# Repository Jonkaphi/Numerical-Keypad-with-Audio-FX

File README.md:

# Mechanical Numerical Keypad with local Audio FX
The desire to make this little keypad came from idea to reuse a some of the parts from a broken keyboard someone gave me.

The extra little feature of having audio fx being played locally on the keyboard with each button press, was from one of the commenters on reddit related to a post. The sound files will be read from the placed SD card. Currently the audio that can be played is from 8 to 16 kHz kHz sample rate with 16 bit signed PCM.

The lower level sd card interface for the file system used in the project was made by Khaled Magdy in their post on 

### Top View

### Bottom View

## Issues as of 08/2025
* Current USB port part is not vertically offset, which collides with the PCB, read "Connectors" page in the schematic.
* Encoder for PC system audio still glitches at times, but its significantly better compared to previous build versions
* Audio streaming and polling of the key inputs is done on a single thread, resulting in less than satisfactory responsiveness

## Future work
* Move to a MCU series that include SDIO for the SD card, has more flash to as to implement some sort of RTOS, and or has a second core to handle the audio streaming.
* General rework of the PCB, redesign of the audio front-end to have better amplification of the DAC data stream.

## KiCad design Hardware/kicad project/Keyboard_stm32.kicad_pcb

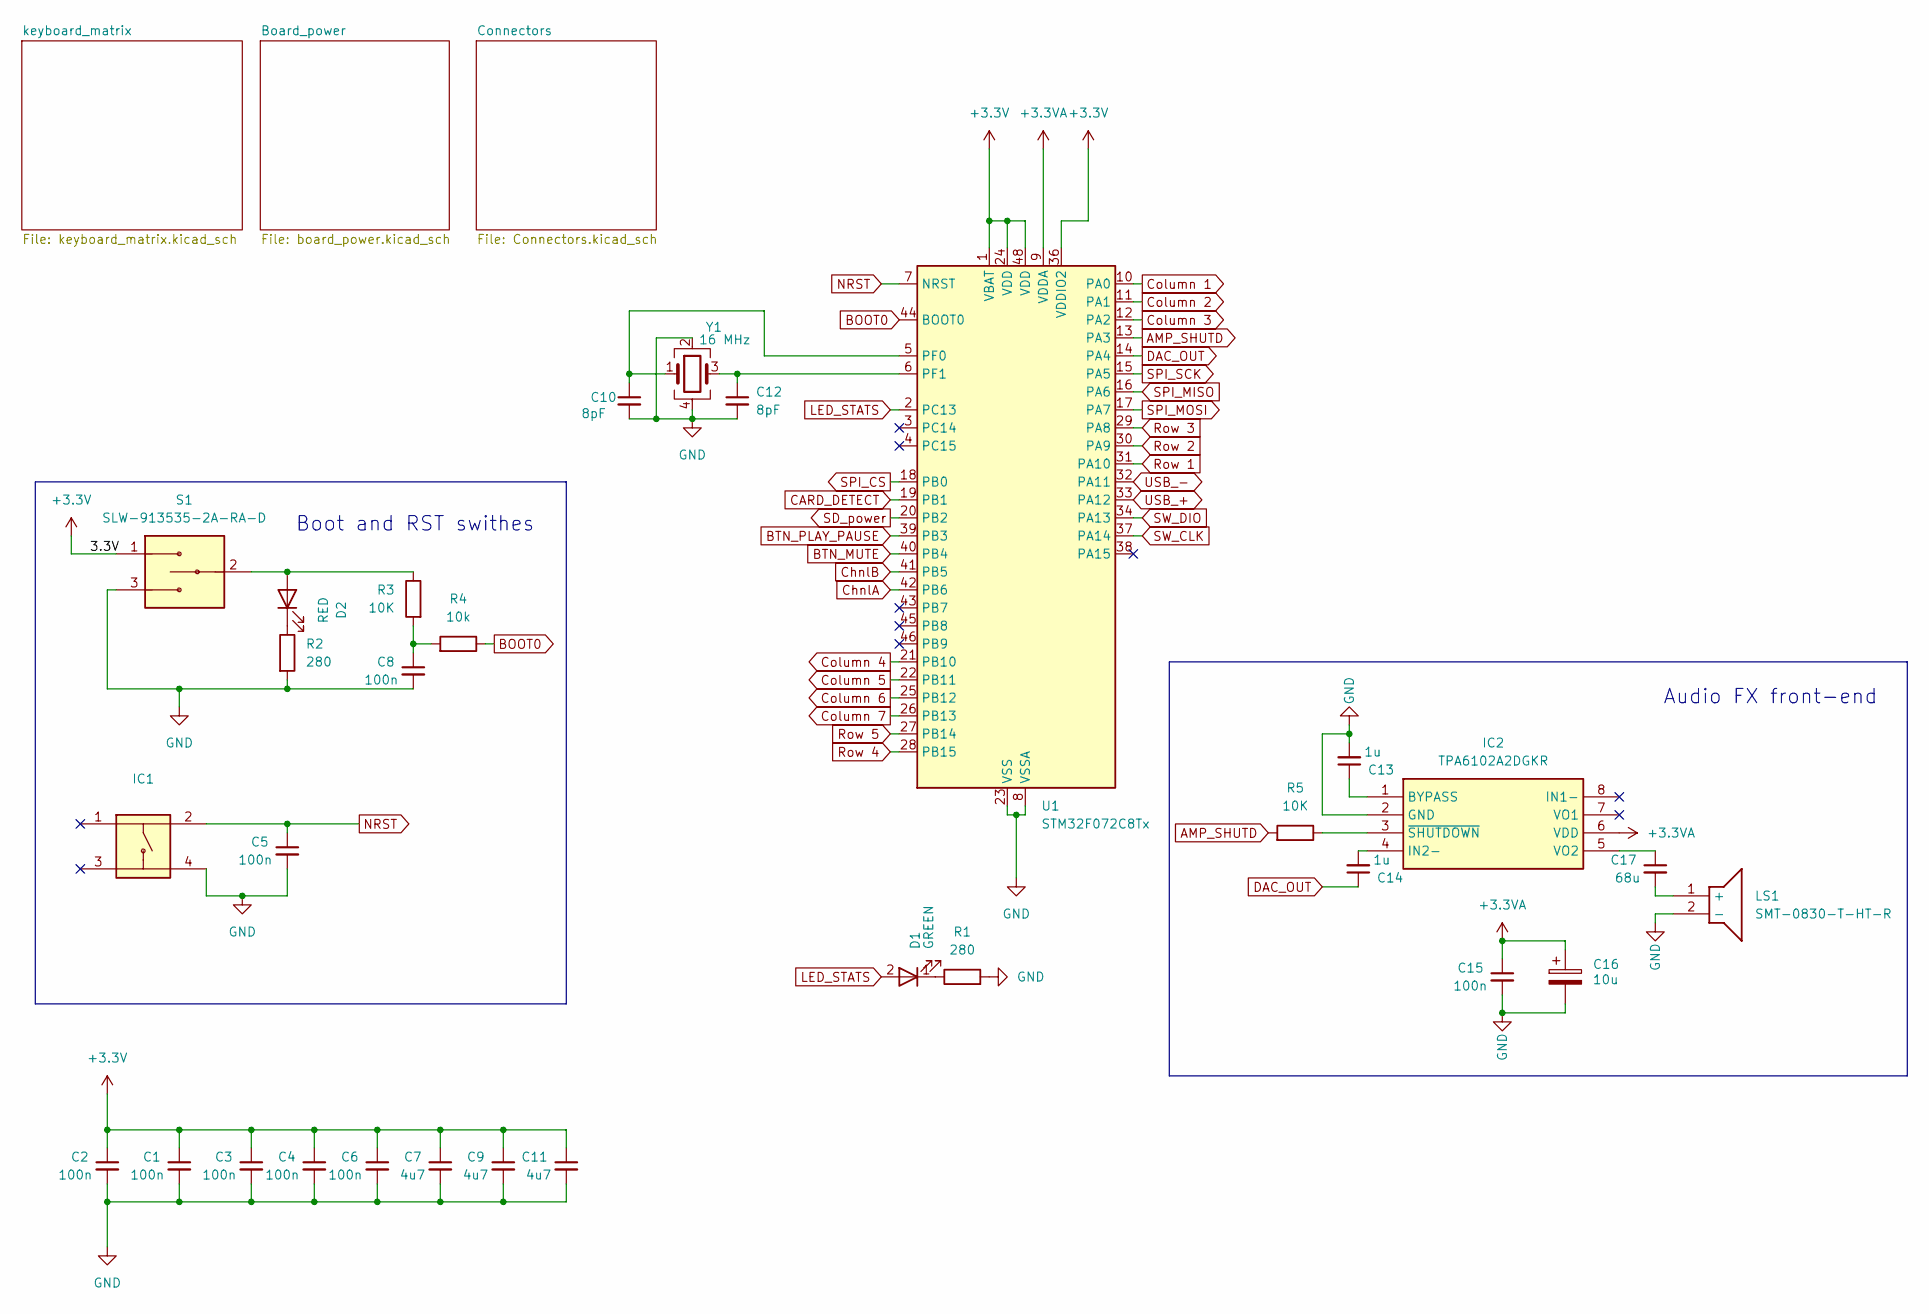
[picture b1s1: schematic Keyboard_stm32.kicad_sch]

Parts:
C1, C2, C3, C4, C5, C6, C8, C15: 100n; C_0805_2012Metric_Pad1.18x1.45mm_HandSolder
C7, C9, C11: 4u7; C_0805_2012Metric_Pad1.18x1.45mm_HandSolder
C10, C12: 8pF; C_0603_1608Metric_Pad1.08x0.95mm_HandSolder
C13, C14: 1u; C_0805_2012Metric_Pad1.18x1.45mm_HandSolder
C16: 10u; CAPPRD200W52D500H1250
C17: 68u; C_1206_3216Metric_Pad1.33x1.80mm_HandSolder
D1: GREEN; 150080VS75000
D2: RED; 150080VS75000
IC1: TS02-66-80-BK-160-LCR-D; TS026680BK160LCRD; Manufacturer_Part_Number TS02-66-80-BK-160-LCR-D; Mouser Part Number 179-TS026680BK160LCR
IC2: TPA6102A2DGKR; SOP65P490X110-8N; Manufacturer_Part_Number TPA6102A2DGKR; Mouser Part Number 595-TPA6102A2DGKR
LS1: SMT-0830-T-HT-R; Manufacturer_Part_Number TE122001-6; Mouser Part Number 497-TE122001-6
R1, R2: 280; R_0603_1608Metric_Pad0.98x0.95mm_HandSolder
R3, R5: 10K; R_0603_1608Metric_Pad0.98x0.95mm_HandSolder
R4: 10k; R_0603_1608Metric_Pad0.98x0.95mm_HandSolder
S1: SLW-913535-2A-RA-D; Manufacturer_Part_Number EG1218; Mouser Part Number 612-EG1218
U1: STM32F072C8Tx; LQFP-48_7x7mm_P0.5mm
Y1: 16 MHz; TSX-3225_16.0000MF09Z-AC3

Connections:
AMP_SHUTD: R5.2, U1.13 (PA3)
BOOT0: R4.1, U1.44 (BOOT0)
BTN_MUTE: U1.40 (PB4); also elsewhere on the board
BTN_PLAY_PAUSE: U1.39 (PB3); also elsewhere on the board
CARD_DETECT: U1.19 (PB1); also elsewhere on the board
ChnlA: U1.42 (PB6); also elsewhere on the board
ChnlB: U1.41 (PB5); also elsewhere on the board
Column 1: U1.10 (PA0); also elsewhere on the board
Column 2: U1.11 (PA1); also elsewhere on the board
Column 3: U1.12 (PA2); also elsewhere on the board
Column 4: U1.21 (PB10); also elsewhere on the board
Column 5: U1.22 (PB11); also elsewhere on the board
Column 6: U1.25 (PB12); also elsewhere on the board
Column 7: U1.26 (PB13); also elsewhere on the board
DAC_OUT: C14.1, U1.14 (PA4)
LED_STATS: D1.2, U1.2 (PC13)
NRST: C5.1, IC1.2, U1.7 (NRST); also elsewhere on the board
unnamed: C8.1, R3.2, R4.2
unnamed: D1.1, R1.1
unnamed: D2.2 (A), R3.1, S1.2
unnamed: D2.1 (K), R2.1
unnamed: C13.1, IC2.1 (BYPASS)
unnamed: C14.2, IC2.4 (IN2-)
unnamed: C17.1, IC2.5 (VO2)
unnamed: IC2.3 (~SHUTDOWN), R5.1
unnamed: C17.2, LS1.1 (+)
unnamed: C10.1, U1.5 (PF0), Y1.1
unnamed: C12.1, U1.6 (PF1), Y1.3
Row 1: U1.31 (PA10); also elsewhere on the board
Row 2: U1.30 (PA9); also elsewhere on the board
Row 3: U1.29 (PA8); also elsewhere on the board
Row 4: U1.28 (PB15); also elsewhere on the board
Row 5: U1.27 (PB14); also elsewhere on the board
SD_power: U1.20 (PB2); also elsewhere on the board
SPI_CS: U1.18 (PB0); also elsewhere on the board
SPI_MISO: U1.16 (PA6); also elsewhere on the board
SPI_MOSI: U1.17 (PA7); also elsewhere on the board
SPI_SCK: U1.15 (PA5); also elsewhere on the board
SW_CLK: U1.37 (PA14); also elsewhere on the board
SW_DIO: U1.34 (PA13); also elsewhere on the board
USB_+: U1.33 (PA12); also elsewhere on the board
USB_-: U1.32 (PA11); also elsewhere on the board

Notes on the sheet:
Boot and RST swithes
Audio FX front-end

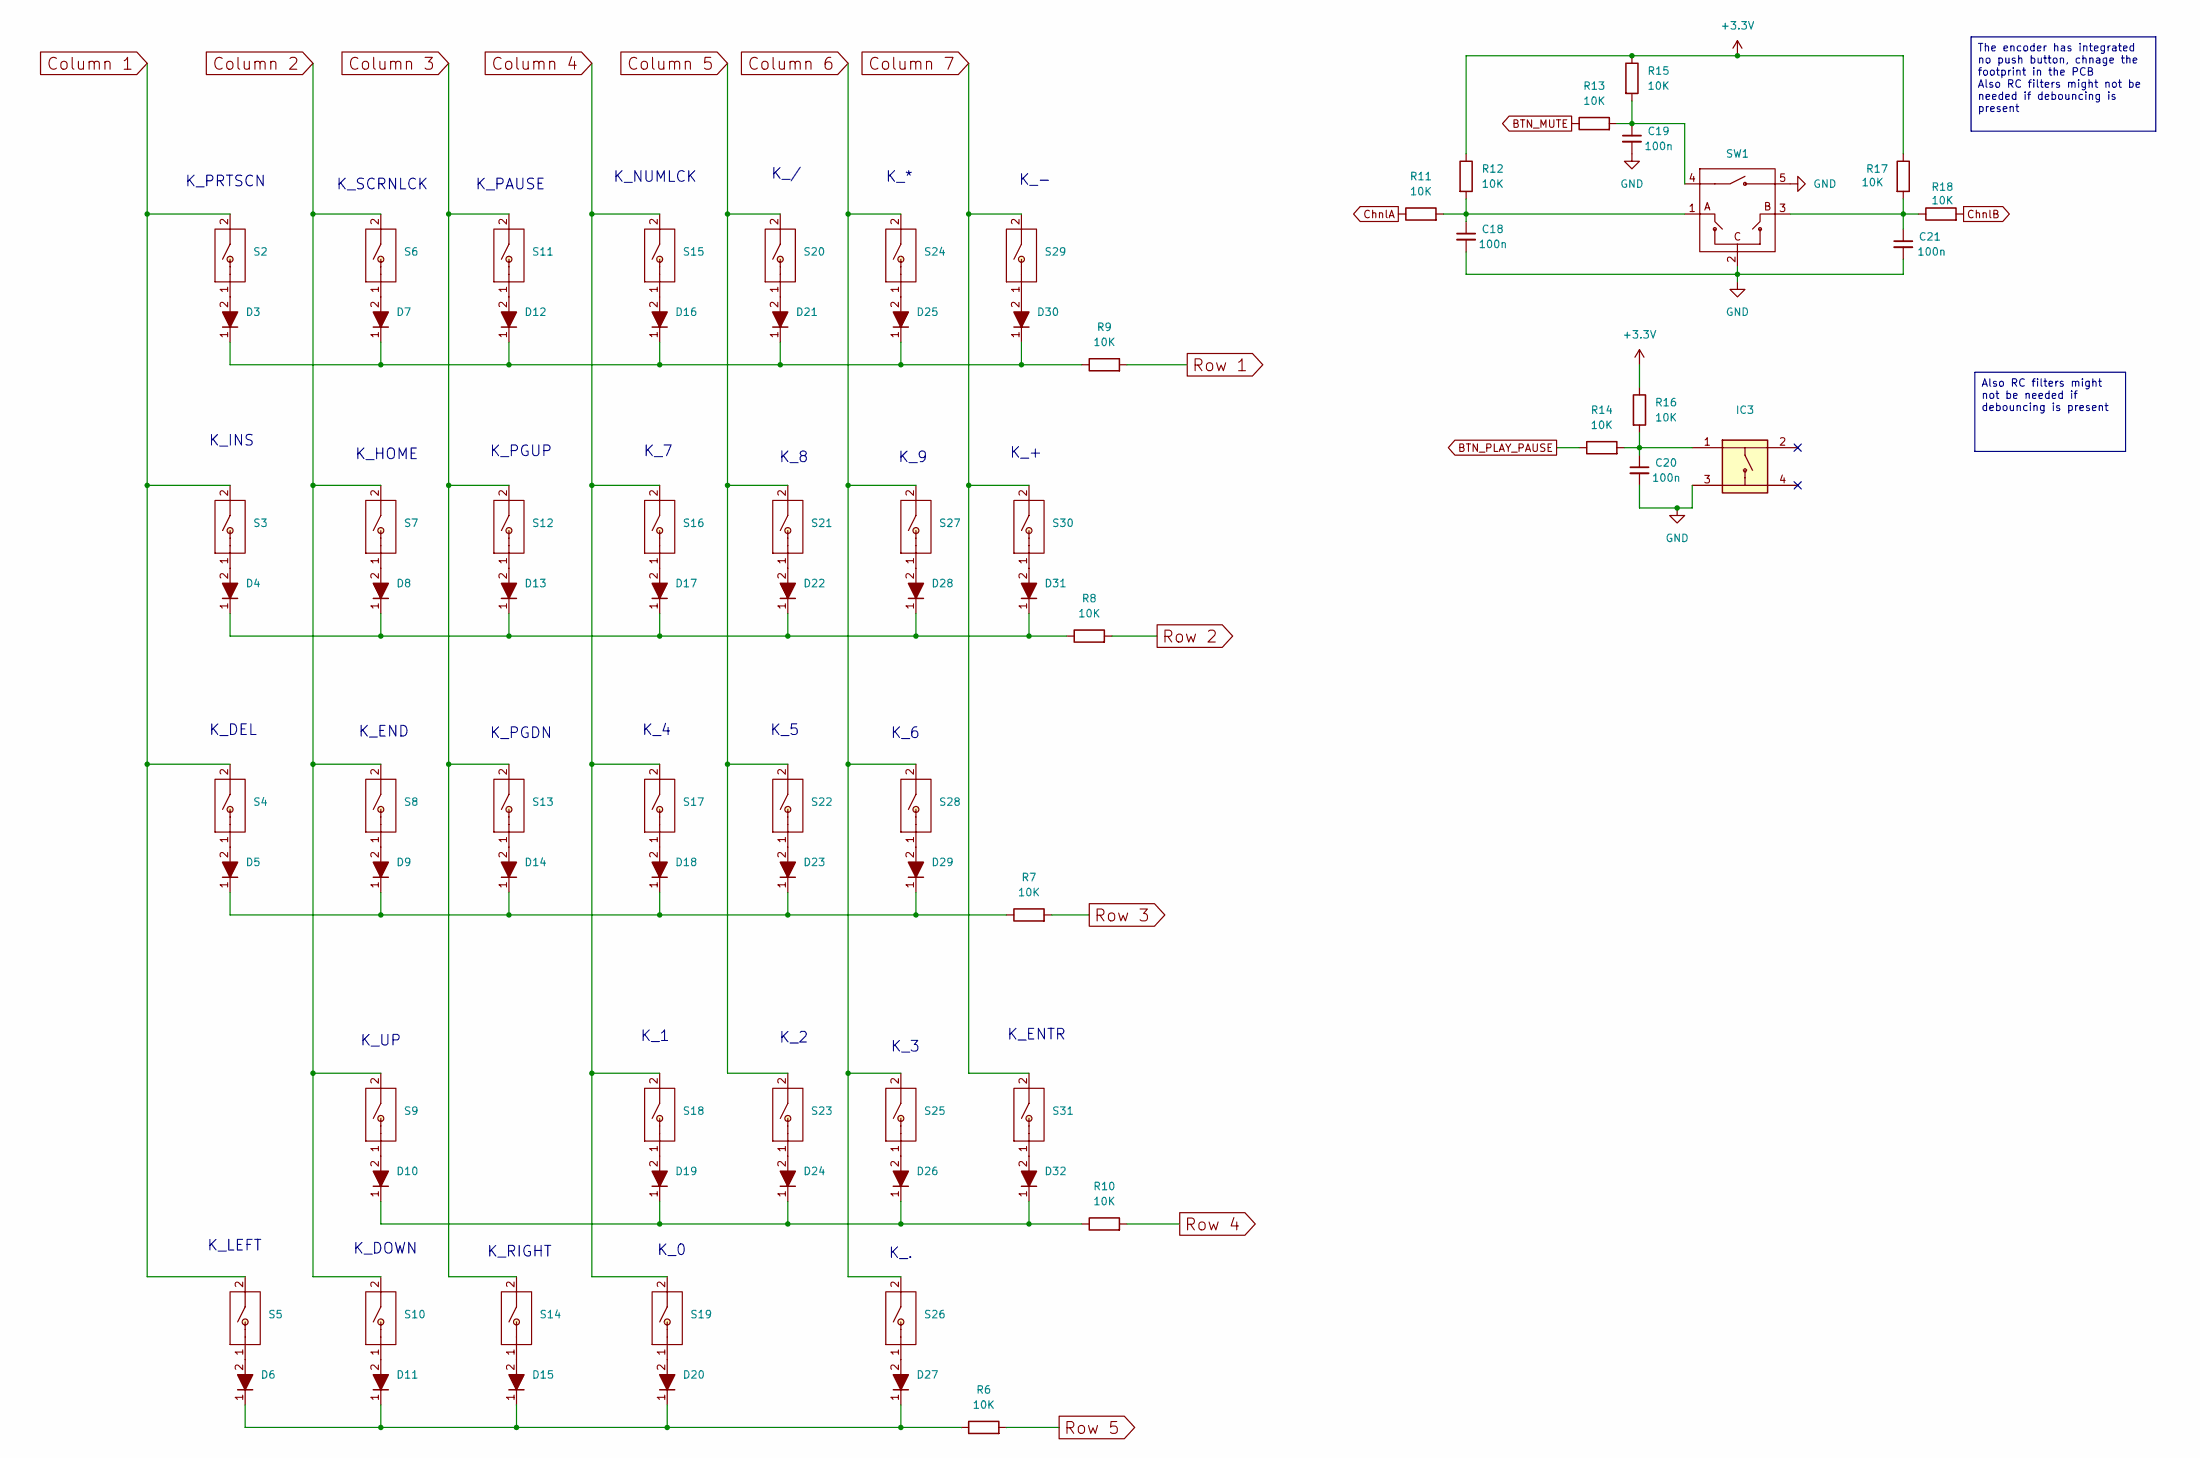
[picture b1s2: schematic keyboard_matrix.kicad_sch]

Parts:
C18, C19, C20, C21: 100n; C_0805_2012Metric_Pad1.18x1.45mm_HandSolder
D3, D4, D5, D6, D7, D8, D9, D10, D11, D12, D13, D14, D15, D16, D17, D18, D19, D20, D21, D22, D23, D24, D25, D26, D27, D28, D29, D30, D31, D32: 1N4148W; SODFL3816X120N; Manufacturer_Part_Number 1N4148W; Mouser Part Number 637-1N4148W
IC3: TS02-66-80-BK-160-LCR-D; TS026680BK160LCRD; Manufacturer_Part_Number TS02-66-80-BK-160-LCR-D; Mouser Part Number 179-TS026680BK160LCR
R6, R7, R8, R9, R10, R11, R12, R13, R14, R15, R16, R17, R18: 10K; R_0603_1608Metric_Pad0.98x0.95mm_HandSolder
S2, S3, S4, S5, S6, S7, S8, S9, S10, S11, S12, S13, S14, S15, S16, S17, S18, S19, S20, S21, S22, S23, S24, S25, S26, S27, S28, S29, S30, S31: Cherry-MX_PCB-Mounted_LTST-A683CEGBW_Kailh_Socket
SW1: PEC12R-4125F-S0012; PEC12R4125FS0012; Manufacturer_Part_Number PEC12R-4125F-S0012; Mouser Part Number 652-PEC12R-4125F-S12

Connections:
BTN_MUTE: R13.1; also elsewhere on the board
BTN_PLAY_PAUSE: R14.1; also elsewhere on the board
ChnlA: R11.1; also elsewhere on the board
ChnlB: R18.2; also elsewhere on the board
Column 1: S2.2, S3.2, S4.2, S5.2; also elsewhere on the board
Column 2: S6.2, S7.2, S8.2, S9.2, S10.2; also elsewhere on the board
Column 3: S11.2, S12.2, S13.2, S14.2; also elsewhere on the board
Column 4: S15.2, S16.2, S17.2, S18.2, S19.2; also elsewhere on the board
Column 5: S20.2, S21.2, S22.2, S23.2; also elsewhere on the board
Column 6: S24.2, S25.2, S26.2, S27.2, S28.2; also elsewhere on the board
Column 7: S29.2, S30.2, S31.2; also elsewhere on the board
unnamed: C18.1, R11.2, R12.2, SW1.1
unnamed: C19.1, R13.2, R15.2, SW1.4
unnamed: C20.1, IC3.1, R14.2, R16.2
unnamed: C21.1, R17.2, R18.1, SW1.3
unnamed: D3.2 (A), S2.1
unnamed: D4.2 (A), S3.1
unnamed: D5.2 (A), S4.1
unnamed: D6.2 (A), S5.1
unnamed: D7.2 (A), S6.1
unnamed: D8.2 (A), S7.1
unnamed: D9.2 (A), S8.1
unnamed: D10.2 (A), S9.1
unnamed: D10.1 (K), D19.1 (K), D24.1 (K), D26.1 (K), D32.1 (K), R10.1
unnamed: D11.2 (A), S10.1
unnamed: D6.1 (K), D11.1 (K), D15.1 (K), D20.1 (K), D27.1 (K), R6.1
unnamed: D12.2 (A), S11.1
unnamed: D3.1 (K), D7.1 (K), D12.1 (K), D16.1 (K), D21.1 (K), D25.1 (K), D30.1 (K), R9.1
unnamed: D13.2 (A), S12.1
unnamed: D4.1 (K), D8.1 (K), D13.1 (K), D17.1 (K), D22.1 (K), D28.1 (K), D31.1 (K), R8.1
unnamed: D14.2 (A), S13.1
unnamed: D5.1 (K), D9.1 (K), D14.1 (K), D18.1 (K), D23.1 (K), D29.1 (K), R7.1
unnamed: D15.2 (A), S14.1
unnamed: D16.2 (A), S15.1
unnamed: D17.2 (A), S16.1
unnamed: D18.2 (A), S17.1
unnamed: D19.2 (A), S18.1
unnamed: D20.2 (A), S19.1
unnamed: D21.2 (A), S20.1
unnamed: D22.2 (A), S21.1
unnamed: D23.2 (A), S22.1
unnamed: D24.2 (A), S23.1
unnamed: D25.2 (A), S24.1
unnamed: D26.2 (A), S25.1
unnamed: D27.2 (A), S26.1
unnamed: D28.2 (A), S27.1
unnamed: D29.2 (A), S28.1
unnamed: D30.2 (A), S29.1
unnamed: D31.2 (A), S30.1
unnamed: D32.2 (A), S31.1
Row 1: R9.2; also elsewhere on the board
Row 2: R8.2; also elsewhere on the board
Row 3: R7.2; also elsewhere on the board
Row 4: R10.2; also elsewhere on the board
Row 5: R6.2; also elsewhere on the board

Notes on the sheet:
The encoder has integrated no push button, chnage the footprint in the PCB Also RC filters might not be needed if debouncing is present
Also RC filters might not be needed if debouncing is present
K_NUMLCK
K_END
K_.
K_7
K_UP
K_ENTR
K_-
K_1
K_4
K_DEL
K_HOME
K_0
K_INS
K_PAUSE
K_9
K_LEFT
K_RIGHT
K_*
K_6
K_8
K_SCRNLCK
K_2
K_PGDN
K_/
K_PGUP
K_PRTSCN
K_3
K_DOWN
K_+
K_5

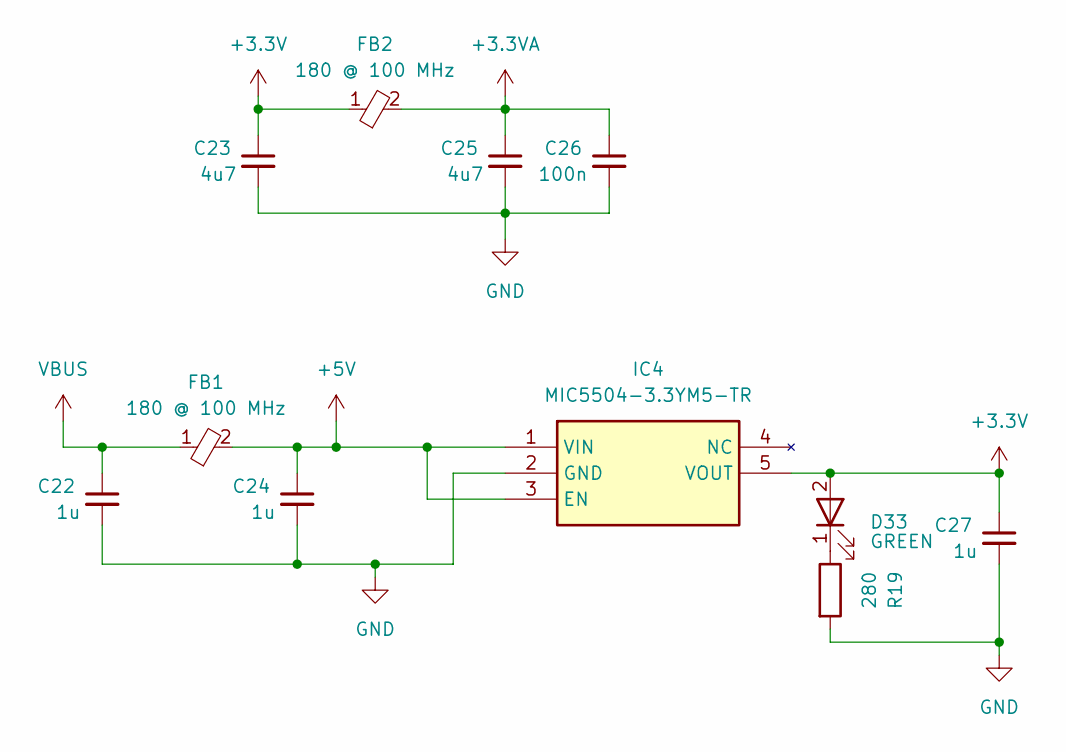
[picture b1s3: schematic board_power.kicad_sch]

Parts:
C22, C24, C27: 1u; C_0805_2012Metric_Pad1.18x1.45mm_HandSolder
C23, C25: 4u7; C_0805_2012Metric_Pad1.18x1.45mm_HandSolder
C26: 100n; C_0805_2012Metric_Pad1.18x1.45mm_HandSolder
D33: GREEN; 150080VS75000
FB1, FB2: 180 @ 100 MHz; ILBB0603ER181V
IC4: MIC5504-3.3YM5-TR; SOT95P280X145-5N; Manufacturer_Part_Number MIC5504-3.3YM5-TR; Mouser Part Number 998-MIC5504-3.3YM5TR
R19: 280; R_0603_1608Metric_Pad0.98x0.95mm_HandSolder

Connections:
+5V: C24.1, FB1.2, IC4.1 (VIN), IC4.3 (EN)
unnamed: D33.1, R19.1
VBUS: C22.1, FB1.1; also elsewhere on the board

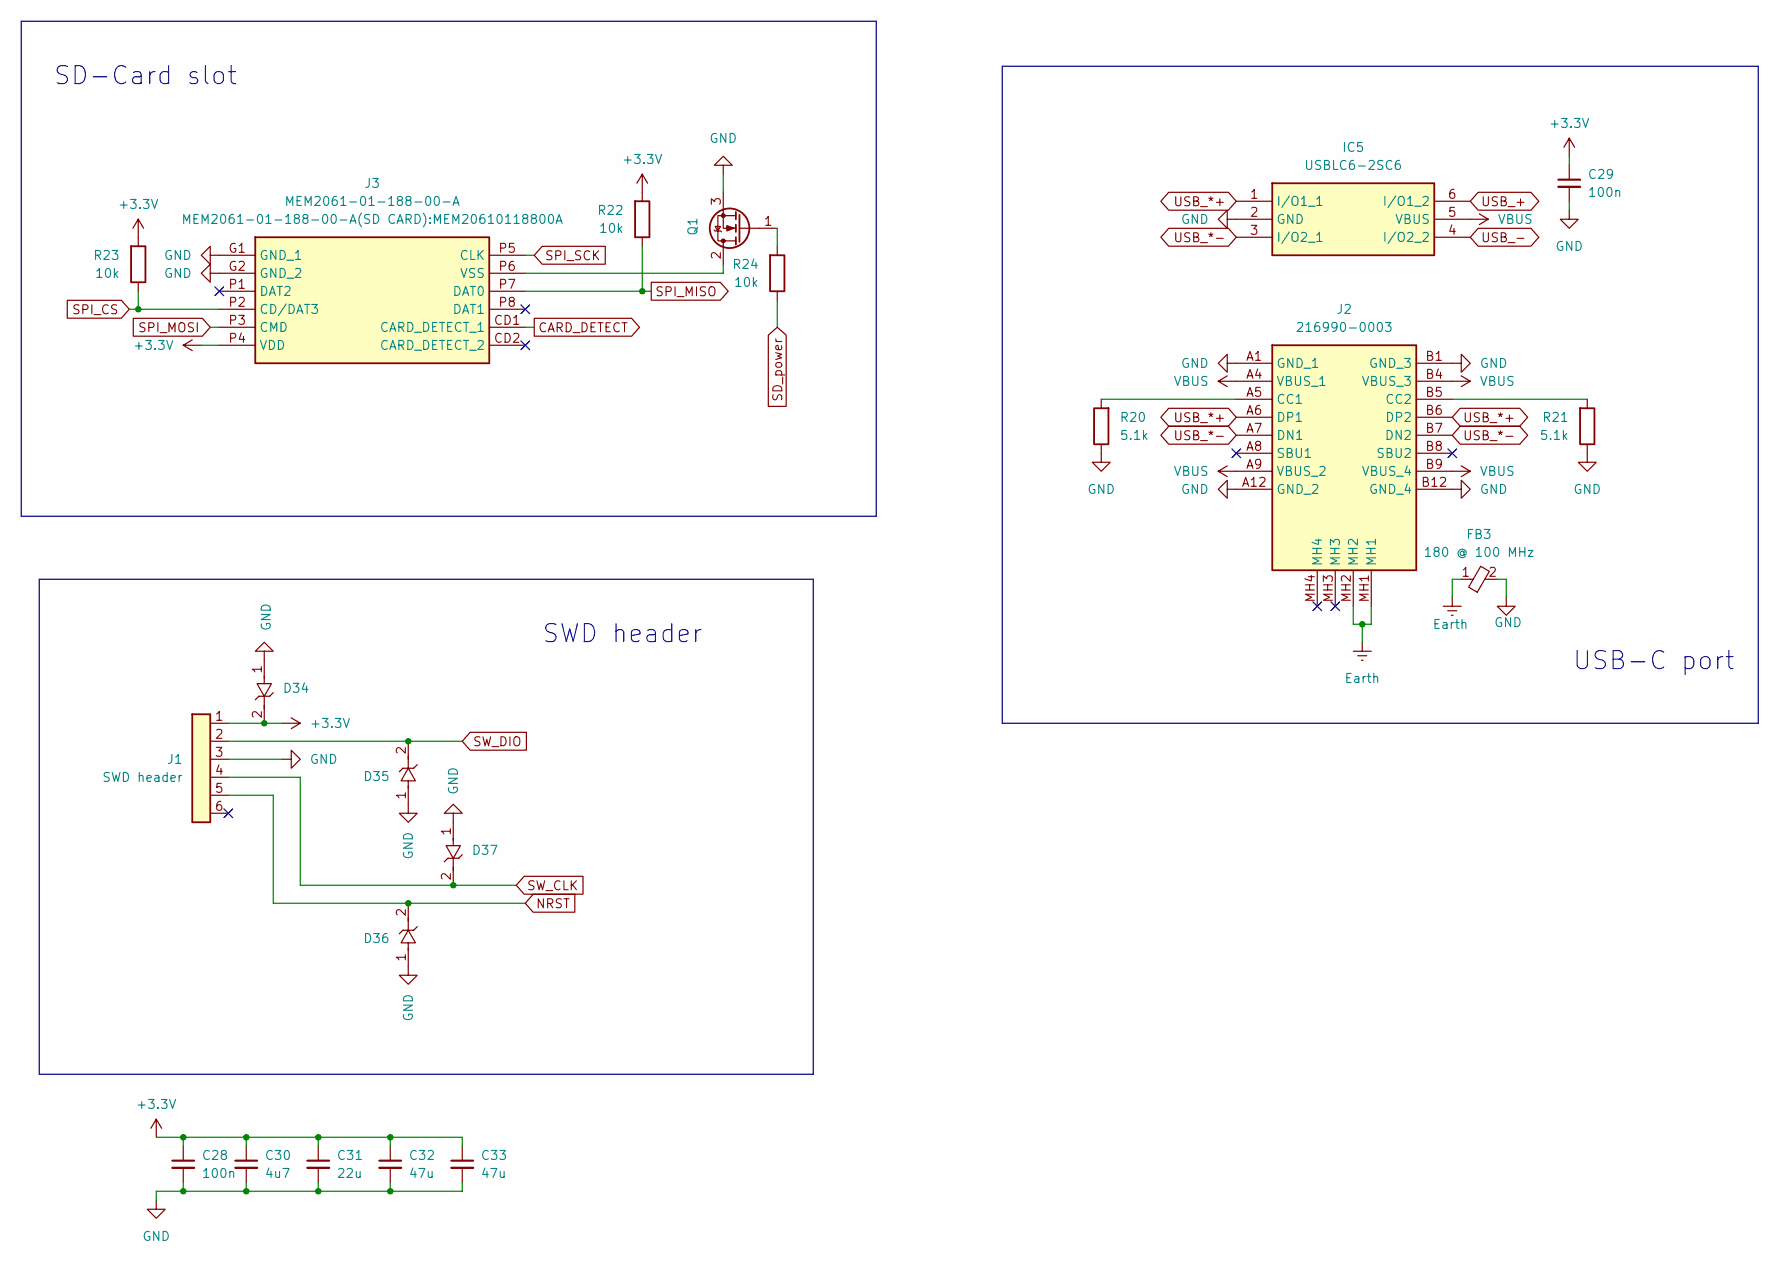
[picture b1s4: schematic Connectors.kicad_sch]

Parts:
C28, C29: 100n; C_0805_2012Metric_Pad1.18x1.45mm_HandSolder
C30: 4u7; C_0805_2012Metric_Pad1.18x1.45mm_HandSolder
C31: 22u; C_0805_2012Metric_Pad1.18x1.45mm_HandSolder
C32, C33: 47u; C_0805_2012Metric_Pad1.18x1.45mm_HandSolder
D34, D35, D36, D37: p4smaj65(DO-214AC)
FB3: 180 @ 100 MHz; ILBB0603ER181V
IC5: USBLC6-2SC6; SOT95P280X145-6N; Manufacturer_Part_Number USBLC6-2SC6; Mouser Part Number 511-USBLC6-2SC6
J1: SWD header; TSW-106-XX-YY-S; Manufacturer_Part_Number TSW-106-07-T-S; Mouser Part Number 200-TSW10607TS
J2: 216990-0003; Manufacturer_Part_Number 216990-0003; Mouser Part Number 538-216990-0003
J3: MEM2061-01-188-00-A; MEM20610118800A; Manufacturer_Part_Number MEM2061-01-188-00-A; Mouser Part Number 640-MEM20610118800A
Q1: BSS316NH6327XTSA1; SOT-23_Handsoldering
R20, R21: 5.1k; R_0603_1608Metric_Pad0.98x0.95mm_HandSolder
R22, R23, R24: 10k; R_0603_1608Metric_Pad0.98x0.95mm_HandSolder

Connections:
CARD_DETECT: J3.CD1 (CARD_DETECT_1); also elsewhere on the board
Earth: FB3.1, J2.MH1, J2.MH2
NRST: D36.2, J1.5; also elsewhere on the board
unnamed: J2.A5 (CC1), R20.2
unnamed: J2.B5 (CC2), R21.2
unnamed: J3.P6 (VSS), Q1.2 (D)
unnamed: Q1.1 (G), R24.2
SD_power: R24.1; also elsewhere on the board
SPI_CS: J3.P2 (CD/DAT3), R23.1; also elsewhere on the board
SPI_MISO: J3.P7 (DAT0), R22.1; also elsewhere on the board
SPI_MOSI: J3.P3 (CMD); also elsewhere on the board
SPI_SCK: J3.P5 (CLK); also elsewhere on the board
SW_CLK: D37.2, J1.4; also elsewhere on the board
SW_DIO: D35.2, J1.2; also elsewhere on the board
USB_*+: IC5.1 (I/O1_1), J2.A6 (DP1), J2.B6 (DP2)
USB_*-: IC5.3 (I/O2_1), J2.A7 (DN1), J2.B7 (DN2)
USB_+: IC5.6 (I/O1_2); also elsewhere on the board
USB_-: IC5.4 (I/O2_2); also elsewhere on the board
VBUS: IC5.5 (VBUS), J2.A4 (VBUS_1), J2.A9 (VBUS_2), J2.B4 (VBUS_3), J2.B9 (VBUS_4); also elsewhere on the board

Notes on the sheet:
USB-C port
SWD header
SD-Card slot

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
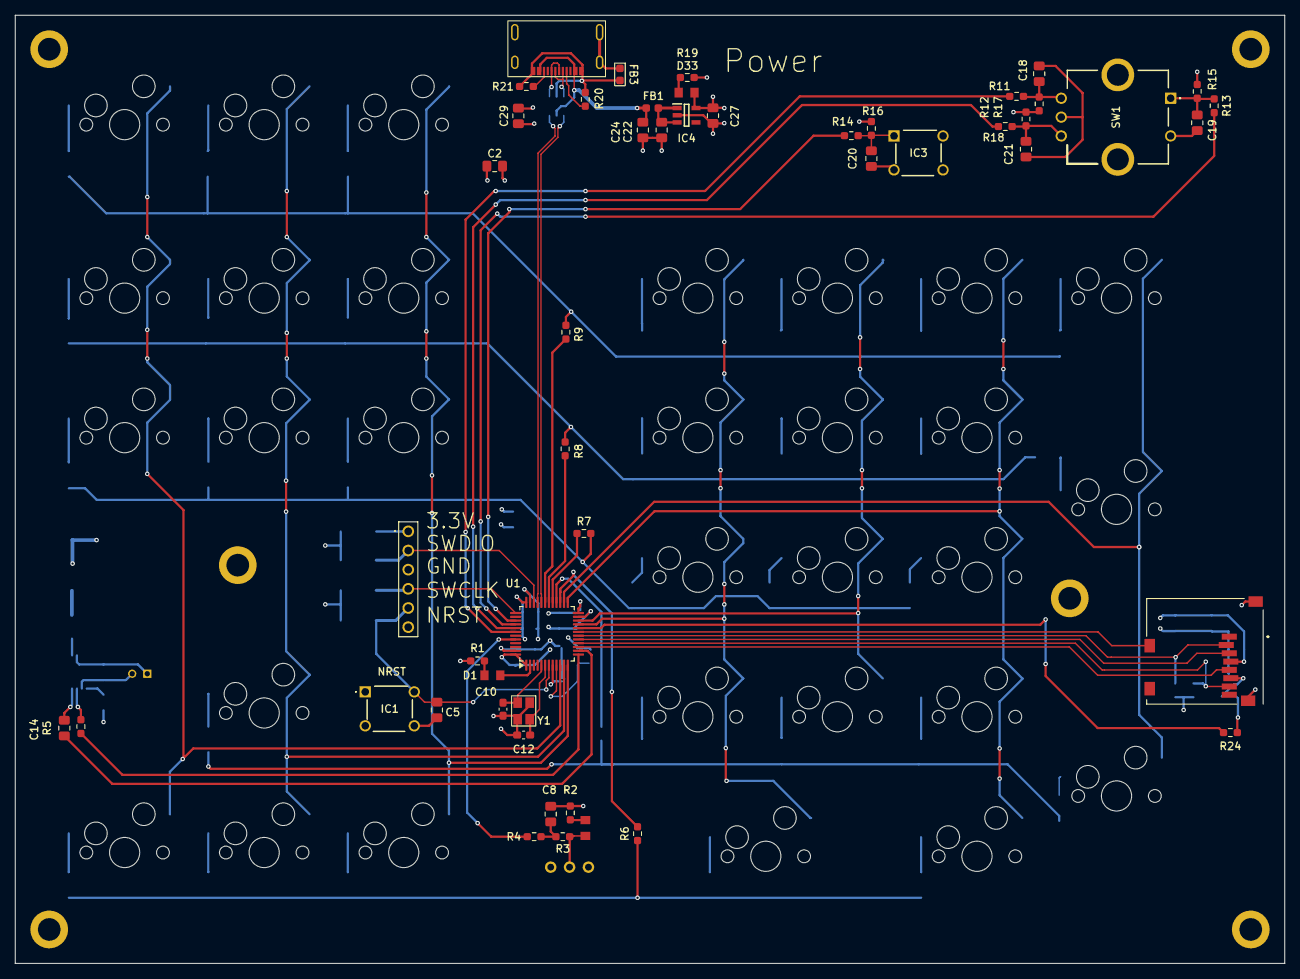
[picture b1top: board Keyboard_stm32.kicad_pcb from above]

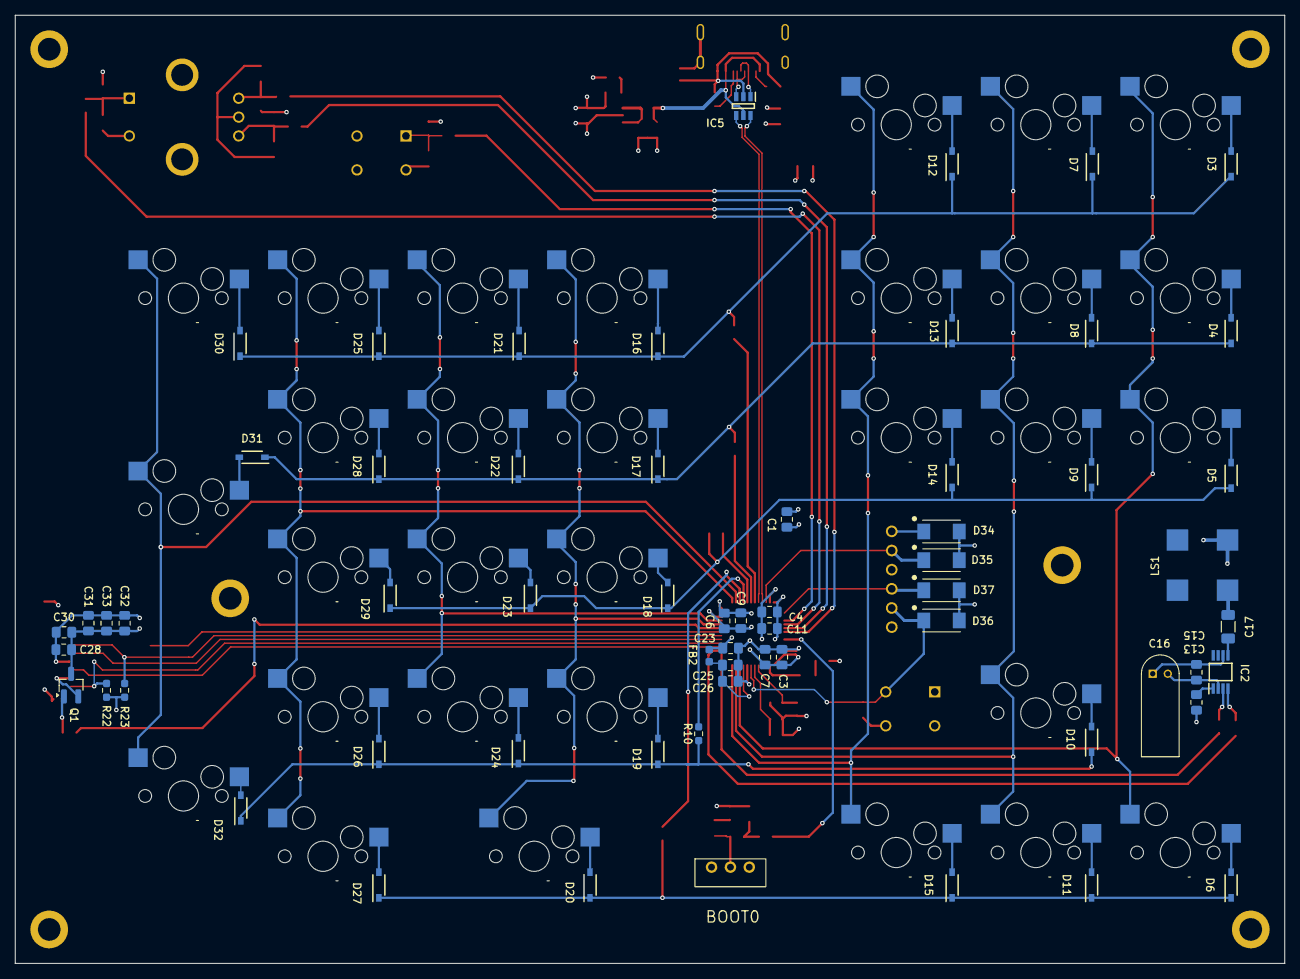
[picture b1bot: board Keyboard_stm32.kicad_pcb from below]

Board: 4 copper layers, 168.3 x 125.7 mm, 141 parts (61 on the bottom side), 96 nets.

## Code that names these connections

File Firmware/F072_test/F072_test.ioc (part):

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Mcu.Name=STM32F072C(8-B)Tx
Mcu.Package=LQFP48
Mcu.UserName=STM32F072C8Tx
PA0.GPIOParameters=GPIO_Label
PA0.GPIO_Label=CLM_1
PA0.Signal=GPIO_Output
PA1.GPIOParameters=GPIO_Label
PA1.GPIO_Label=CLM_2
PA1.Signal=GPIO_Output
PA10.GPIOParameters=GPIO_PuPd,GPIO_Label
PA10.GPIO_Label=ROW_1
PA10.GPIO_PuPd=GPIO_PULLDOWN
PA10.Signal=GPIO_Input
PA11.Mode=Device
PA11.Signal=USB_DM
PA12.Mode=Device
PA12.Signal=USB_DP
PA13.Mode=Serial_Wire
PA13.Signal=SYS_SWDIO
PA14.Mode=Serial_Wire
PA14.Signal=SYS_SWCLK
PA2.GPIOParameters=GPIO_Label
PA2.GPIO_Label=CLM_3
PA2.Signal=GPIO_Output
PA3.GPIOParameters=GPIO_Label
PA3.GPIO_Label=AMP_SHUTDWN
PA3.Signal=GPIO_Output
PA4.Signal=COMP_DAC1_group
PA5.Mode=Full_Duplex_Master
PA5.Signal=SPI1_SCK
PA6.Mode=Full_Duplex_Master
PA6.Signal=SPI1_MISO
PA7.Mode=Full_Duplex_Master
PA7.Signal=SPI1_MOSI
PA8.GPIOParameters=GPIO_PuPd,GPIO_Label
PA8.GPIO_Label=ROW_3
PA8.GPIO_PuPd=GPIO_PULLDOWN
PA8.Signal=GPIO_Input
PA9.GPIOParameters=GPIO_PuPd,GPIO_Label
PA9.GPIO_Label=ROW_2
PA9.GPIO_PuPd=GPIO_PULLDOWN
PA9.Signal=GPIO_Input
PB0.GPIOParameters=GPIO_Label
PB0.GPIO_Label=SPI_CS
PB0.Signal=GPIO_Output
PB1.GPIOParameters=GPIO_PuPd,GPIO_Label
PB1.GPIO_Label=CARD_detect
PB1.GPIO_PuPd=GPIO_PULLDOWN
PB1.Signal=GPIO_Input
PB10.GPIOParameters=GPIO_Label
PB10.GPIO_Label=CLM_4
PB10.Signal=GPIO_Output
PB11.GPIOParameters=GPIO_Label
PB11.GPIO_Label=CLM_5
PB11.Signal=GPIO_Output
PB12.GPIOParameters=GPIO_Label
PB12.GPIO_Label=CLM_6
PB12.Signal=GPIO_Output
PB13.GPIOParameters=GPIO_Label
PB13.GPIO_Label=CLM_7
PB13.Signal=GPIO_Output
PB14.GPIOParameters=GPIO_PuPd,GPIO_Label
PB14.GPIO_Label=ROW_5
PB14.GPIO_PuPd=GPIO_PULLDOWN
PB14.Signal=GPIO_Input
PB15.GPIOParameters=GPIO_PuPd,GPIO_Label
PB15.GPIO_Label=ROW_4
PB15.GPIO_PuPd=GPIO_PULLDOWN
PB15.Signal=GPIO_Input
PB2.GPIOParameters=GPIO_Label
PB2.GPIO_Label=CARD_SHUTDOWN
PB2.Signal=GPIO_Output
PB3.GPIOParameters=GPIO_PuPd,GPIO_Label
PB3.GPIO_Label=PLAY_PAUSE
PB3.GPIO_PuPd=GPIO_PULLDOWN
PB3.Signal=GPIO_Input
PB4.GPIOParameters=GPIO_PuPd,GPIO_Label
PB4.GPIO_Label=MUTE
PB4.GPIO_PuPd=GPIO_PULLDOWN
PB4.Signal=GPIO_Input
PB5.GPIOParameters=GPIO_PuPd,GPIO_Label
PB5.GPIO_Label=ENC_B
PB5.GPIO_PuPd=GPIO_PULLDOWN
PB5.Signal=GPIO_Input
PB6.GPIOParameters=GPIO_PuPd,GPIO_Label
PB6.GPIO_Label=ENC_A
PB6.GPIO_PuPd=GPIO_PULLDOWN
PB6.Signal=GPIO_Input
PC13.GPIOParameters=GPIO_Label
PC13.GPIO_Label=LED_STAT
PC13.Signal=GPIO_Output
PF0-OSC_IN.Mode=HSE-External-Oscillator
PF0-OSC_IN.Signal=RCC_OSC_IN
PF1-OSC_OUT.Mode=HSE-External-Oscillator
PF1-OSC_OUT.Signal=RCC_OSC_OUT
RCC.HSE_VALUE=16000000
RCC.SYSCLKFreq_VALUE=48000000
RCC.SYSCLKSource=RCC_SYSCLKSOURCE_PLLCLK
board=custom

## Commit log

2025-07-10 updated files, added PDF versions on schematic and PCB
2025-07-10 moved files around
2025-07-11 added notes to mistake on PCB
2025-07-23 First commit from private version, previous commit was a mistake
2025-07-25 merged with priv. repo
    This version has now a working file system, although only made for text files
2025-08-06 Added small comments to the problems of the schematic, SD card.
2025-09-10 First Commit, from private
